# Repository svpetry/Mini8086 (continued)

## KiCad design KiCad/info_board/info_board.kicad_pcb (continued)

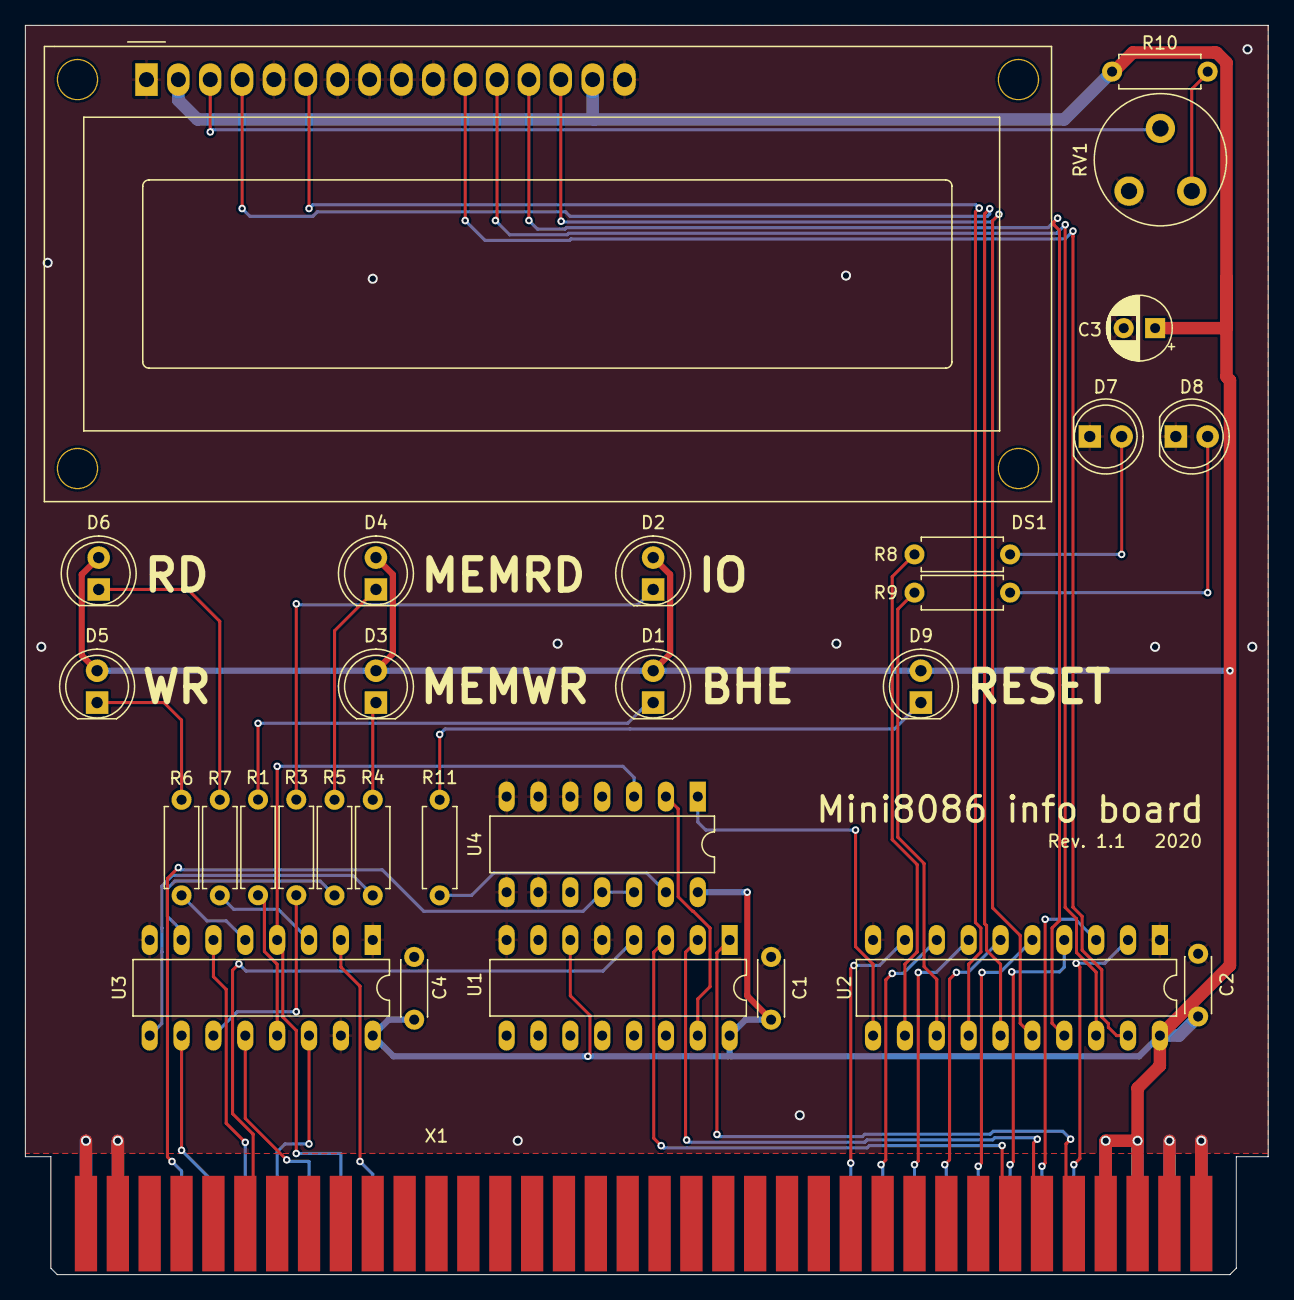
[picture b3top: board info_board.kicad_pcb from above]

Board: 2 copper layers, 99.1 x 99.6 mm, 30 parts (0 on the bottom side), 49 nets.

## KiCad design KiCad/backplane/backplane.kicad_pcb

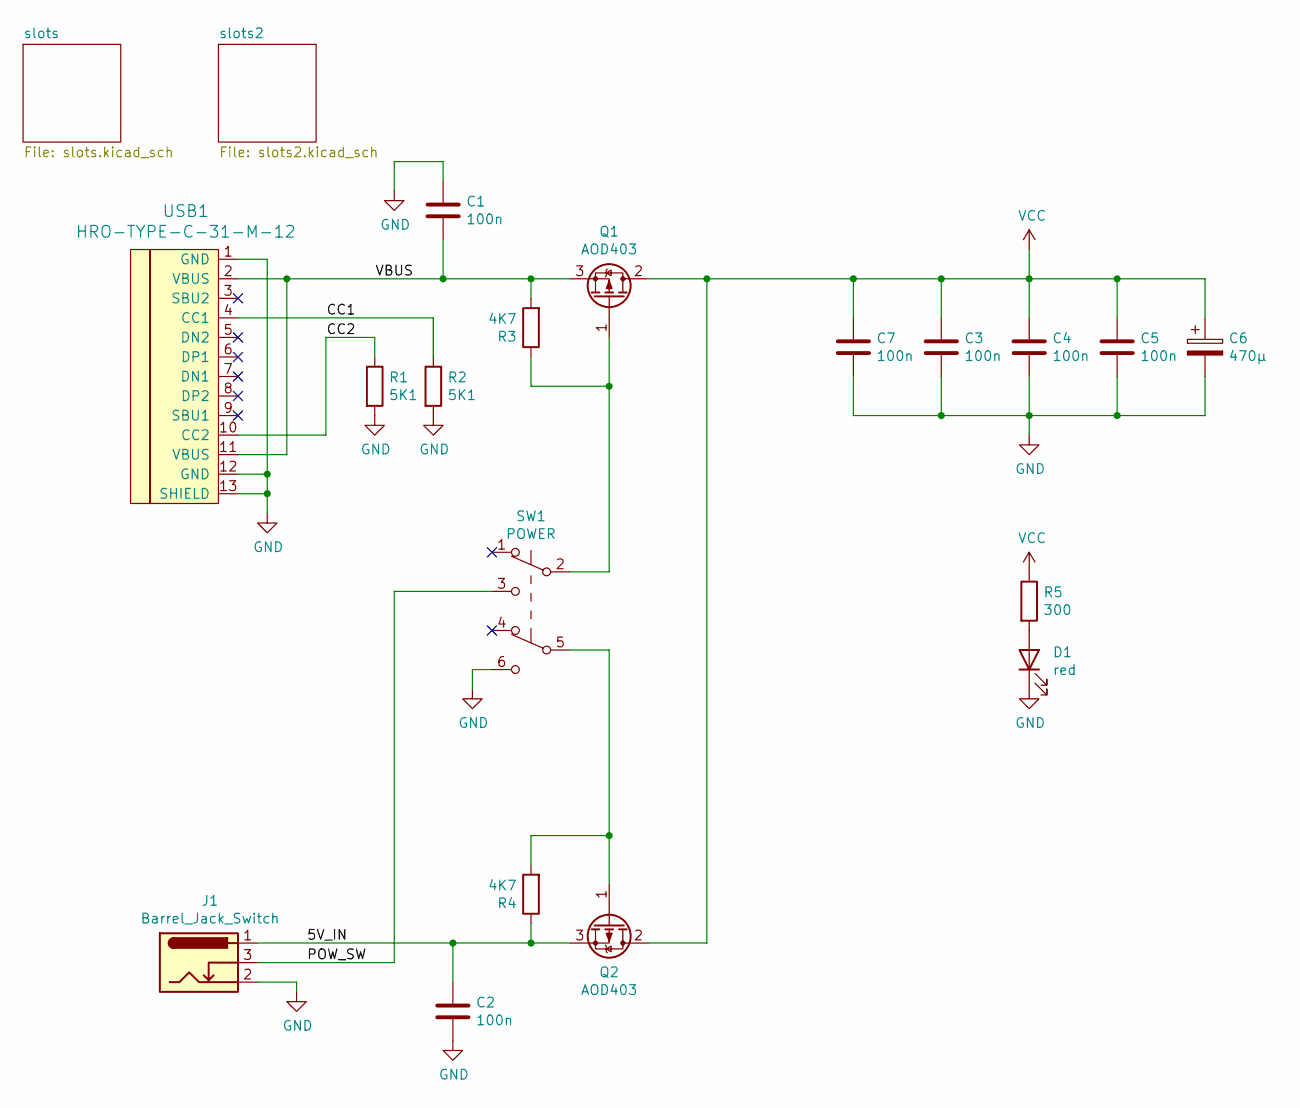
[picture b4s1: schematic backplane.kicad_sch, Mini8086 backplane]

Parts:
C1, C2: 100n; C_1206_3216Metric
C3, C4, C5, C7: 100n; C_Disc_D5.0mm_W2.5mm_P5.00mm
C6: 470µ; CP_Radial_D8.0mm_P3.80mm
D1: red; LED_1206_3216Metric_Castellated
J1: Barrel_Jack_Switch; BarrelJack_Horizontal
Q1, Q2: AOD403; TO-252-2
R1, R2: 5K1; R_1206_3216Metric
R3, R4: 4K7; R_1206_3216Metric
R5: 300; R_1206_3216Metric
SW1: POWER; Button
USB1: HRO-TYPE-C-31-M-12

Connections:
/5V_IN: C2.1, J1.1, Q2.3 (S), R4.1
/CC1: R2.1, USB1.4 (CC1)
/CC2: R1.1, USB1.10 (CC2)
/POW_SW: J1.3, SW1.3 (C)
/VBUS: C1.2, Q1.3 (S), R3.2, USB1.2 (VBUS), USB1.11 (VBUS)
GND: C1.1, C2.2, C3.2, C4.2, C5.2, C6.2, C7.2, D1.1 (K), J1.2, R1.2, R2.2, SW1.6 (C), USB1.1 (GND), USB1.12 (GND), USB1.13 (SHIELD); also elsewhere on the board
unnamed: D1.2 (A), R5.2
unnamed: Q1.1 (G), R3.1, SW1.2 (B)
unnamed: Q2.1 (G), R4.2, SW1.5 (B)
VCC: C3.1, C4.1, C5.1, C6.1, C7.1, Q1.2 (D), Q2.2 (D), R5.1; also elsewhere on the board

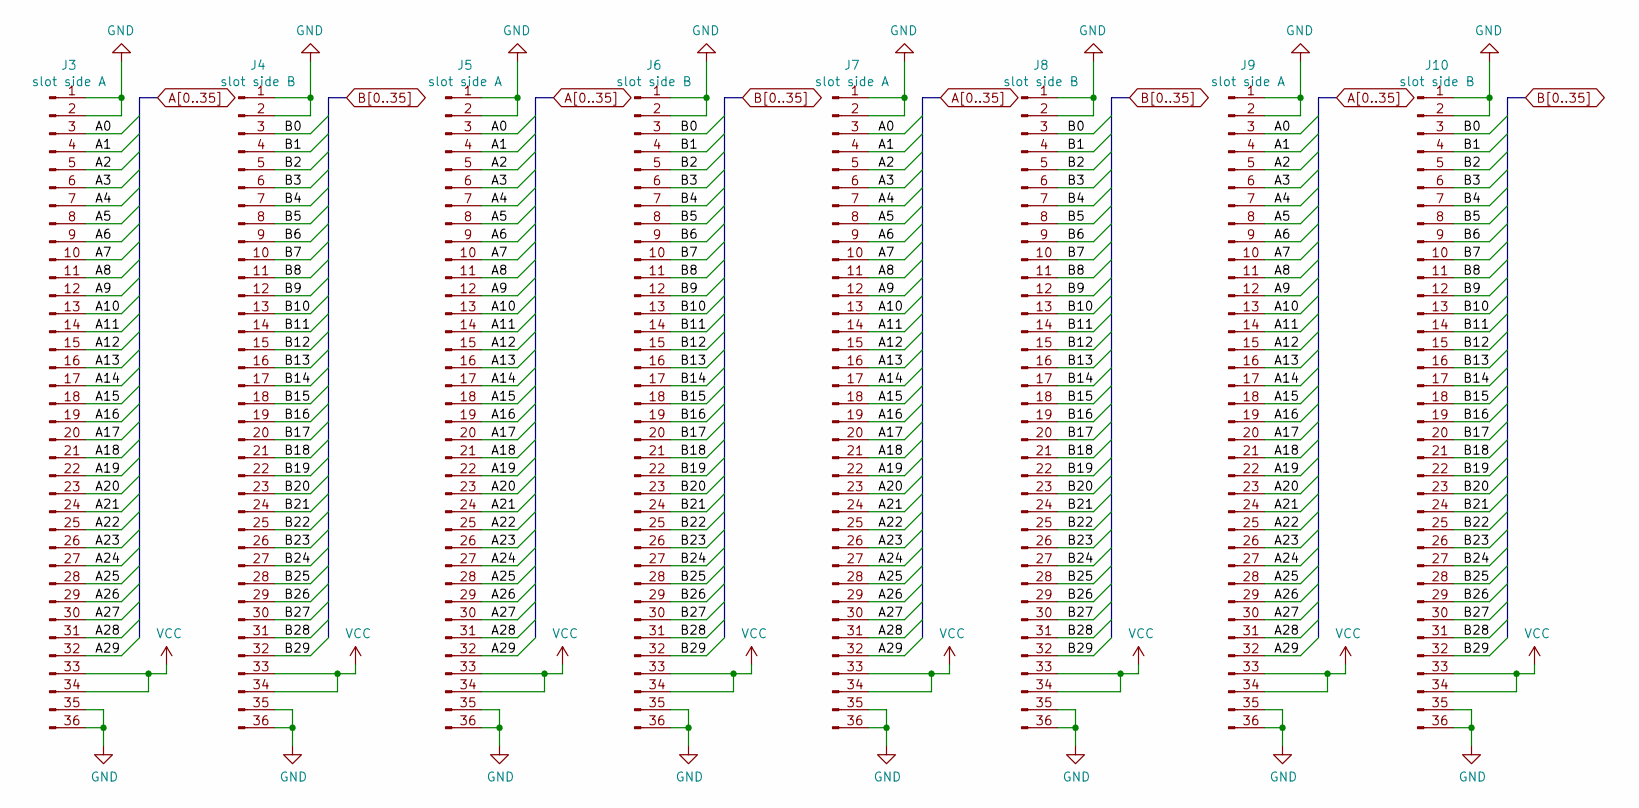
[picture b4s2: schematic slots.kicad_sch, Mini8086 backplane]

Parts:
J3, J5, J7, J9: slot side A; PinHeader_1x36_P2.54mm_Vertical
J4, J6, J8, J10: slot side B; PinHeader_1x36_P2.54mm_Vertical

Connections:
A0: J3.3, J5.3, J7.3, J9.3; also elsewhere on the board
A1: J3.4, J5.4, J7.4, J9.4; also elsewhere on the board
A2: J3.5, J5.5, J7.5, J9.5; also elsewhere on the board
A3: J3.6, J5.6, J7.6, J9.6; also elsewhere on the board
A4: J3.7, J5.7, J7.7, J9.7; also elsewhere on the board
A5: J3.8, J5.8, J7.8, J9.8; also elsewhere on the board
A6: J3.9, J5.9, J7.9, J9.9; also elsewhere on the board
A7: J3.10, J5.10, J7.10, J9.10; also elsewhere on the board
A8: J3.11, J5.11, J7.11, J9.11; also elsewhere on the board
A9: J3.12, J5.12, J7.12, J9.12; also elsewhere on the board
A10: J3.13, J5.13, J7.13, J9.13; also elsewhere on the board
A11: J3.14, J5.14, J7.14, J9.14; also elsewhere on the board
A12: J3.15, J5.15, J7.15, J9.15; also elsewhere on the board
A13: J3.16, J5.16, J7.16, J9.16; also elsewhere on the board
A14: J3.17, J5.17, J7.17, J9.17; also elsewhere on the board
A15: J3.18, J5.18, J7.18, J9.18; also elsewhere on the board
A16: J3.19, J5.19, J7.19, J9.19; also elsewhere on the board
A17: J3.20, J5.20, J7.20, J9.20; also elsewhere on the board
A18: J3.21, J5.21, J7.21, J9.21; also elsewhere on the board
A19: J3.22, J5.22, J7.22, J9.22; also elsewhere on the board
A20: J3.23, J5.23, J7.23, J9.23; also elsewhere on the board
A21: J3.24, J5.24, J7.24, J9.24; also elsewhere on the board
A22: J3.25, J5.25, J7.25, J9.25; also elsewhere on the board
A23: J3.26, J5.26, J7.26, J9.26; also elsewhere on the board
A24: J3.27, J5.27, J7.27, J9.27; also elsewhere on the board
A25: J3.28, J5.28, J7.28, J9.28; also elsewhere on the board
A26: J3.29, J5.29, J7.29, J9.29; also elsewhere on the board
A27: J3.30, J5.30, J7.30, J9.30; also elsewhere on the board
A28: J3.31, J5.31, J7.31, J9.31; also elsewhere on the board
A29: J3.32, J5.32, J7.32, J9.32; also elsewhere on the board
B0: J4.3, J6.3, J8.3, J10.3; also elsewhere on the board
B1: J4.4, J6.4, J8.4, J10.4; also elsewhere on the board
B2: J4.5, J6.5, J8.5, J10.5; also elsewhere on the board
B3: J4.6, J6.6, J8.6, J10.6; also elsewhere on the board
B4: J4.7, J6.7, J8.7, J10.7; also elsewhere on the board
B5: J4.8, J6.8, J8.8, J10.8; also elsewhere on the board
B6: J4.9, J6.9, J8.9, J10.9; also elsewhere on the board
B7: J4.10, J6.10, J8.10, J10.10; also elsewhere on the board
B8: J4.11, J6.11, J8.11, J10.11; also elsewhere on the board
B9: J4.12, J6.12, J8.12, J10.12; also elsewhere on the board
B10: J4.13, J6.13, J8.13, J10.13; also elsewhere on the board
B11: J4.14, J6.14, J8.14, J10.14; also elsewhere on the board
B12: J4.15, J6.15, J8.15, J10.15; also elsewhere on the board
B13: J4.16, J6.16, J8.16, J10.16; also elsewhere on the board
B14: J4.17, J6.17, J8.17, J10.17; also elsewhere on the board
B15: J4.18, J6.18, J8.18, J10.18; also elsewhere on the board
B16: J4.19, J6.19, J8.19, J10.19; also elsewhere on the board
B17: J4.20, J6.20, J8.20, J10.20; also elsewhere on the board
B18: J4.21, J6.21, J8.21, J10.21; also elsewhere on the board
B19: J4.22, J6.22, J8.22, J10.22; also elsewhere on the board
B20: J4.23, J6.23, J8.23, J10.23; also elsewhere on the board
B21: J4.24, J6.24, J8.24, J10.24; also elsewhere on the board
B22: J4.25, J6.25, J8.25, J10.25; also elsewhere on the board
B23: J4.26, J6.26, J8.26, J10.26; also elsewhere on the board
B24: J4.27, J6.27, J8.27, J10.27; also elsewhere on the board
B25: J4.28, J6.28, J8.28, J10.28; also elsewhere on the board
B26: J4.29, J6.29, J8.29, J10.29; also elsewhere on the board
B27: J4.30, J6.30, J8.30, J10.30; also elsewhere on the board
B28: J4.31, J6.31, J8.31, J10.31; also elsewhere on the board
B29: J4.32, J6.32, J8.32, J10.32; also elsewhere on the board
GND: J3.1, J3.2, J3.35, J3.36, J4.1, J4.2, J4.35, J4.36, J5.1, J5.2, J5.35, J5.36, J6.1, J6.2, J6.35, J6.36, J7.1, J7.2, J7.35, J7.36, J8.1, J8.2, J8.35, J8.36, J9.1, J9.2, J9.35, J9.36, J10.1, J10.2, J10.35, J10.36; also elsewhere on the board
VCC: J3.33, J3.34, J4.33, J4.34, J5.33, J5.34, J6.33, J6.34, J7.33, J7.34, J8.33, J8.34, J9.33, J9.34, J10.33, J10.34; also elsewhere on the board

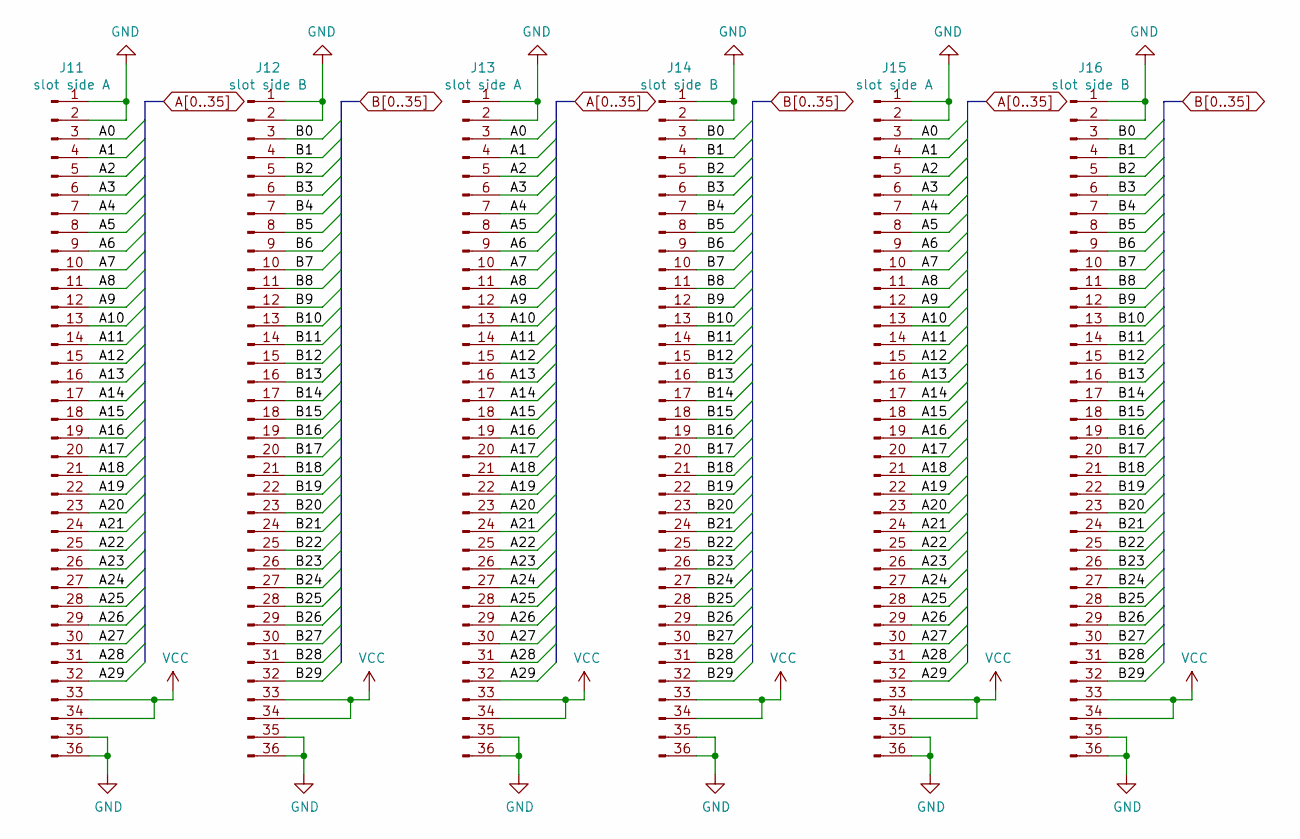
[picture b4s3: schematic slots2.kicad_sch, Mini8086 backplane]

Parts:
J11, J13, J15: slot side A; PinHeader_1x36_P2.54mm_Vertical
J12, J14, J16: slot side B; PinHeader_1x36_P2.54mm_Vertical

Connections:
A0: J11.3, J13.3, J15.3; also elsewhere on the board
A1: J11.4, J13.4, J15.4; also elsewhere on the board
A2: J11.5, J13.5, J15.5; also elsewhere on the board
A3: J11.6, J13.6, J15.6; also elsewhere on the board
A4: J11.7, J13.7, J15.7; also elsewhere on the board
A5: J11.8, J13.8, J15.8; also elsewhere on the board
A6: J11.9, J13.9, J15.9; also elsewhere on the board
A7: J11.10, J13.10, J15.10; also elsewhere on the board
A8: J11.11, J13.11, J15.11; also elsewhere on the board
A9: J11.12, J13.12, J15.12; also elsewhere on the board
A10: J11.13, J13.13, J15.13; also elsewhere on the board
A11: J11.14, J13.14, J15.14; also elsewhere on the board
A12: J11.15, J13.15, J15.15; also elsewhere on the board
A13: J11.16, J13.16, J15.16; also elsewhere on the board
A14: J11.17, J13.17, J15.17; also elsewhere on the board
A15: J11.18, J13.18, J15.18; also elsewhere on the board
A16: J11.19, J13.19, J15.19; also elsewhere on the board
A17: J11.20, J13.20, J15.20; also elsewhere on the board
A18: J11.21, J13.21, J15.21; also elsewhere on the board
A19: J11.22, J13.22, J15.22; also elsewhere on the board
A20: J11.23, J13.23, J15.23; also elsewhere on the board
A21: J11.24, J13.24, J15.24; also elsewhere on the board
A22: J11.25, J13.25, J15.25; also elsewhere on the board
A23: J11.26, J13.26, J15.26; also elsewhere on the board
A24: J11.27, J13.27, J15.27; also elsewhere on the board
A25: J11.28, J13.28, J15.28; also elsewhere on the board
A26: J11.29, J13.29, J15.29; also elsewhere on the board
A27: J11.30, J13.30, J15.30; also elsewhere on the board
A28: J11.31, J13.31, J15.31; also elsewhere on the board
A29: J11.32, J13.32, J15.32; also elsewhere on the board
B0: J12.3, J14.3, J16.3; also elsewhere on the board
B1: J12.4, J14.4, J16.4; also elsewhere on the board
B2: J12.5, J14.5, J16.5; also elsewhere on the board
B3: J12.6, J14.6, J16.6; also elsewhere on the board
B4: J12.7, J14.7, J16.7; also elsewhere on the board
B5: J12.8, J14.8, J16.8; also elsewhere on the board
B6: J12.9, J14.9, J16.9; also elsewhere on the board
B7: J12.10, J14.10, J16.10; also elsewhere on the board
B8: J12.11, J14.11, J16.11; also elsewhere on the board
B9: J12.12, J14.12, J16.12; also elsewhere on the board
B10: J12.13, J14.13, J16.13; also elsewhere on the board
B11: J12.14, J14.14, J16.14; also elsewhere on the board
B12: J12.15, J14.15, J16.15; also elsewhere on the board
B13: J12.16, J14.16, J16.16; also elsewhere on the board
B14: J12.17, J14.17, J16.17; also elsewhere on the board
B15: J12.18, J14.18, J16.18; also elsewhere on the board
B16: J12.19, J14.19, J16.19; also elsewhere on the board
B17: J12.20, J14.20, J16.20; also elsewhere on the board
B18: J12.21, J14.21, J16.21; also elsewhere on the board
B19: J12.22, J14.22, J16.22; also elsewhere on the board
B20: J12.23, J14.23, J16.23; also elsewhere on the board
B21: J12.24, J14.24, J16.24; also elsewhere on the board
B22: J12.25, J14.25, J16.25; also elsewhere on the board
B23: J12.26, J14.26, J16.26; also elsewhere on the board
B24: J12.27, J14.27, J16.27; also elsewhere on the board
B25: J12.28, J14.28, J16.28; also elsewhere on the board
B26: J12.29, J14.29, J16.29; also elsewhere on the board
B27: J12.30, J14.30, J16.30; also elsewhere on the board
B28: J12.31, J14.31, J16.31; also elsewhere on the board
B29: J12.32, J14.32, J16.32; also elsewhere on the board
GND: J11.1, J11.2, J11.35, J11.36, J12.1, J12.2, J12.35, J12.36, J13.1, J13.2, J13.35, J13.36, J14.1, J14.2, J14.35, J14.36, J15.1, J15.2, J15.35, J15.36, J16.1, J16.2, J16.35, J16.36; also elsewhere on the board
VCC: J11.33, J11.34, J12.33, J12.34, J13.33, J13.34, J14.33, J14.34, J15.33, J15.34, J16.33, J16.34; also elsewhere on the board

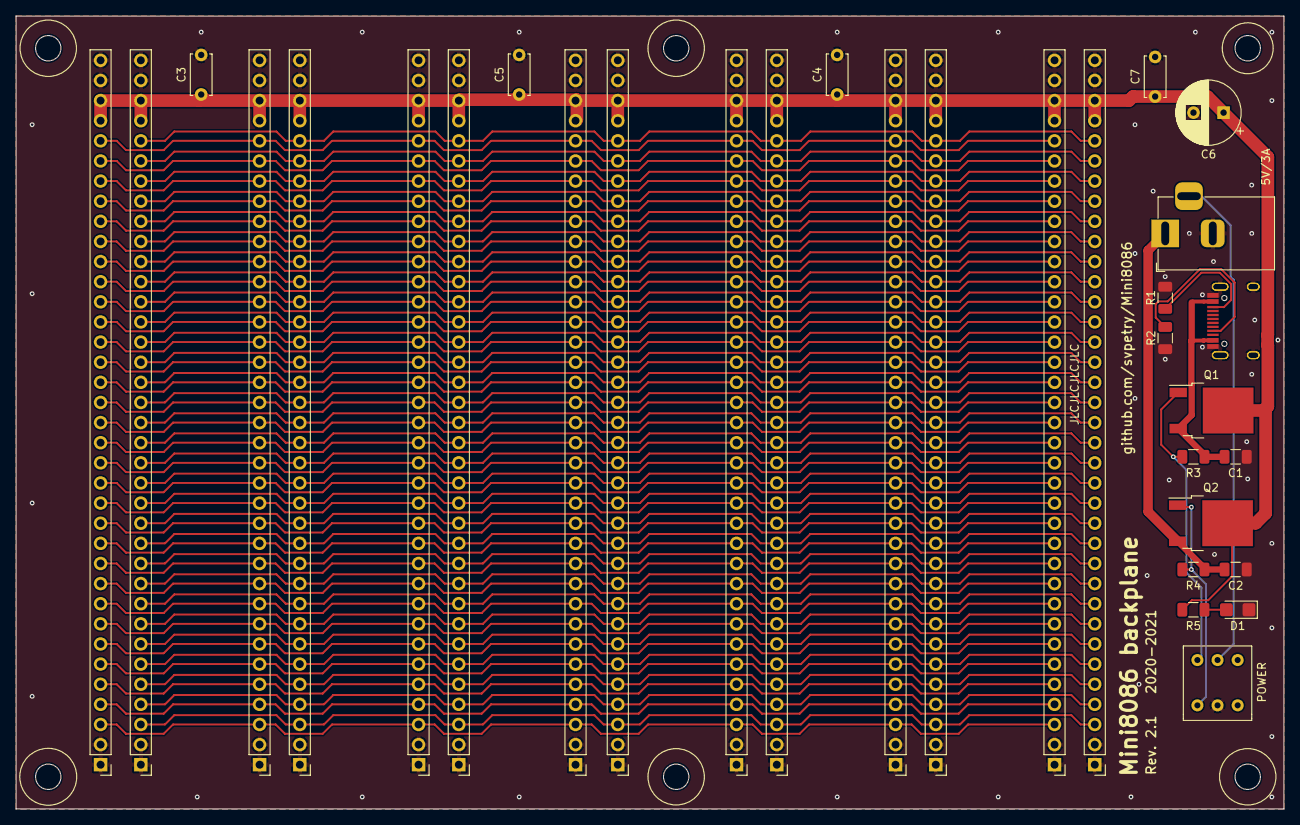
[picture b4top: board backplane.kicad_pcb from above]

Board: 2 copper layers, 160.0 x 100.1 mm, 32 parts (0 on the bottom side), 70 nets.

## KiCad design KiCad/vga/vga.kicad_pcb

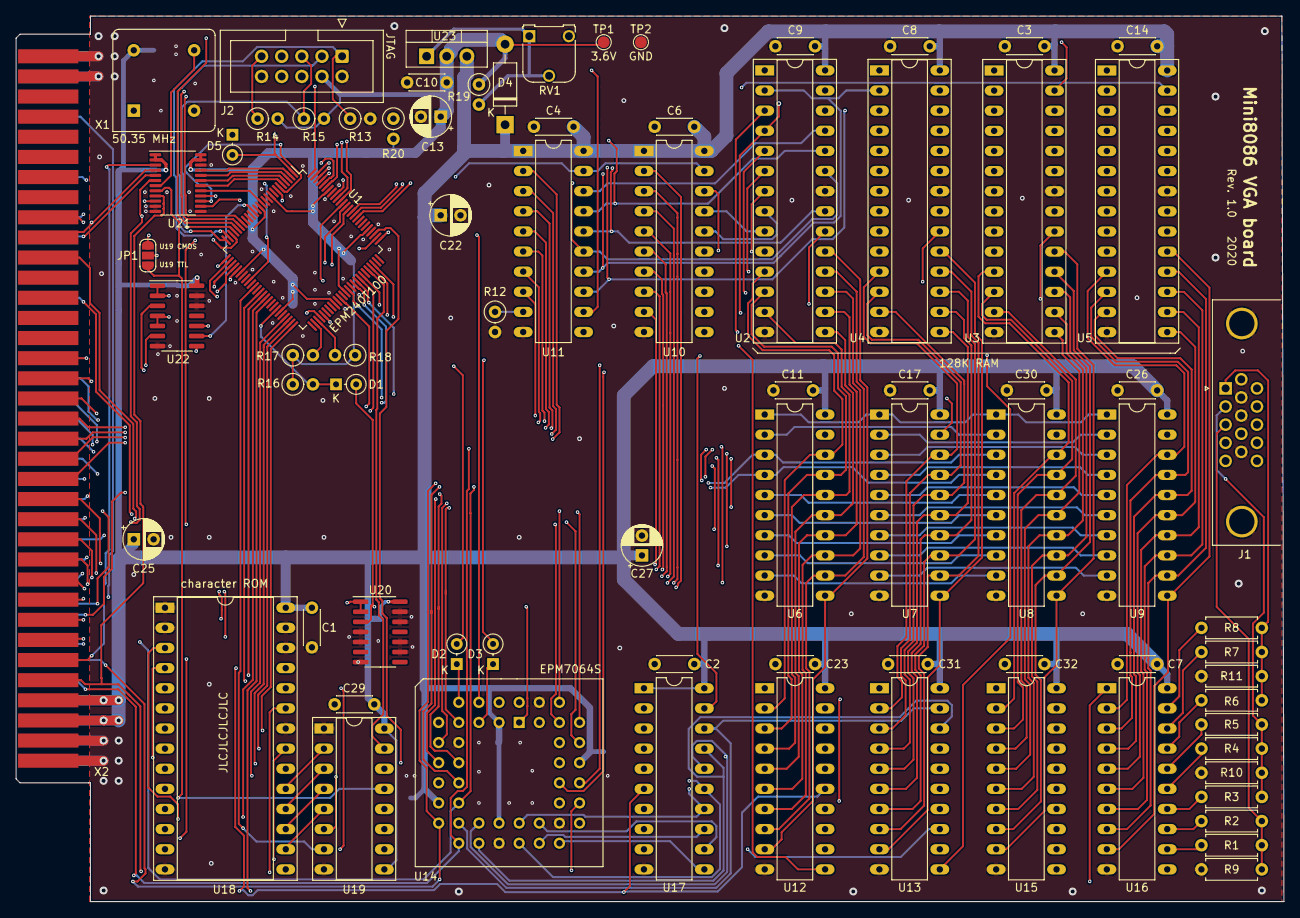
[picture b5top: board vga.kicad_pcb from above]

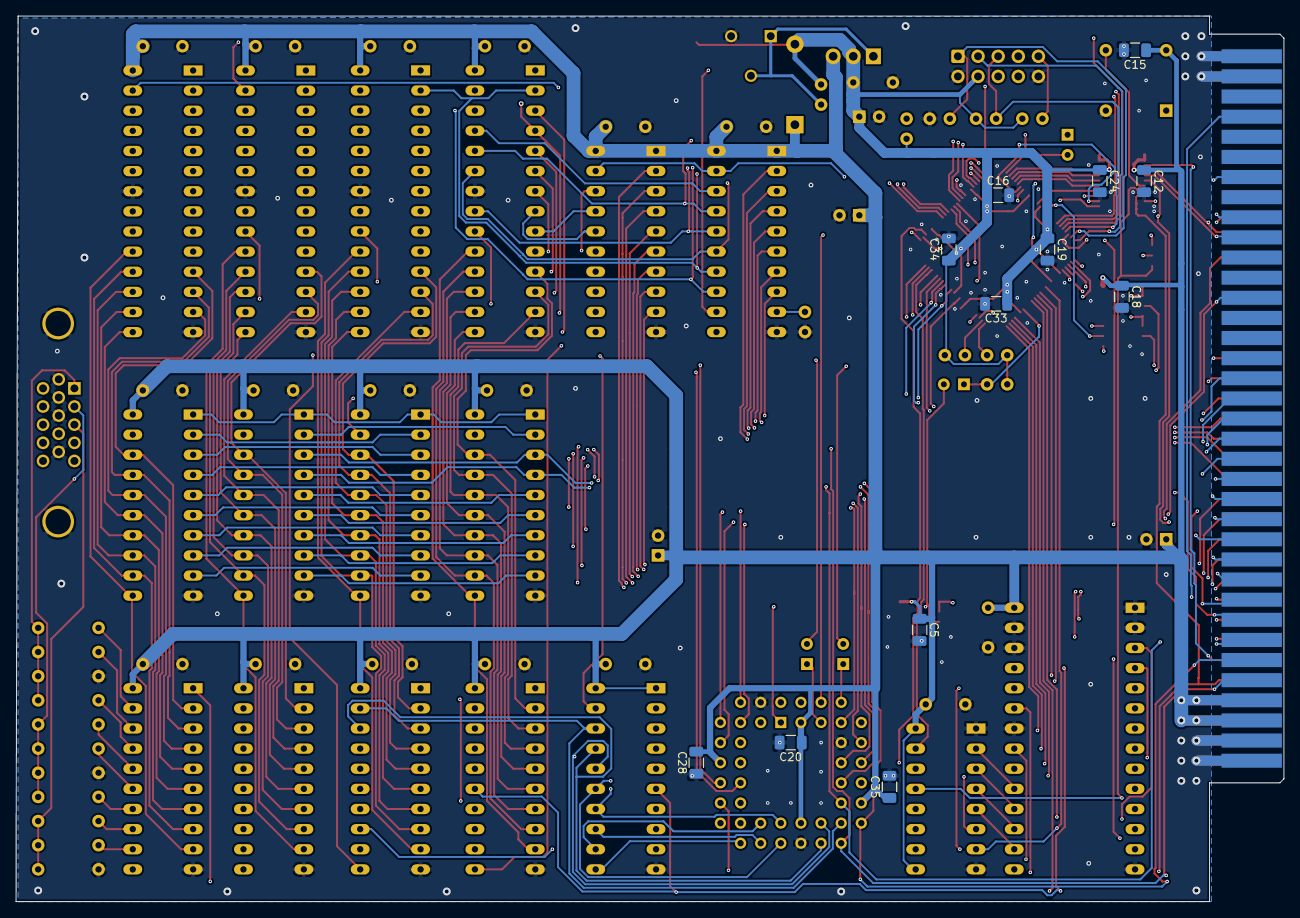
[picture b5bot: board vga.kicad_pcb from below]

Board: 4 copper layers, 160.0 x 111.8 mm, 90 parts (12 on the bottom side), 177 nets.

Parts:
C1, C2, C3, C4, C6, C7, C8, C9, C10, C11, C14, C17, C23, C26, C29, C30, C31, C32: 100n; C_Disc_D4.3mm_W1.9mm_P5.00mm
C5, C12, C15, C16, C18, C19, C20, C24, C28, C33, C34, C35: 100n; C_1206_3216Metric
C13, C25, C27: 10µ; CP_Radial_D5.0mm_P2.50mm
C22: 47µ; CP_Radial_D5.0mm_P2.50mm
D1, D2, D3, D5: BAT43; D_DO-34_SOD68_P2.54mm_Vertical_KathodeUp
D4: 1N4001; D_DO-41_SOD81_P10.16mm_Horizontal
J1: VGA connector; DSUB-15-HD_Female_Horizontal_P2.29x1.98mm_EdgePinOffset3.03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
J2: JTAG; IDC-Header_2x05_P2.54mm_Vertical
JP1: CHARPIXEL; SolderJumper-3_P1.3mm_Open_RoundedPad1.0x1.5mm_NumberLabels
R1, R3, R6: 500; R_Axial_DIN0207_L6.3mm_D2.5mm_P7.62mm_Horizontal
R2, R4, R7: 1K; R_Axial_DIN0207_L6.3mm_D2.5mm_P7.62mm_Horizontal
R5, R8: 2K; R_Axial_DIN0207_L6.3mm_D2.5mm_P7.62mm_Horizontal
R9: 56; R_Axial_DIN0207_L6.3mm_D2.5mm_P7.62mm_Horizontal
R10, R11: 47; R_Axial_DIN0207_L6.3mm_D2.5mm_P7.62mm_Horizontal
R12: 4K7; R_Axial_DIN0207_L6.3mm_D2.5mm_P2.54mm_Vertical
R13: 2K2; R_Axial_DIN0207_L6.3mm_D2.5mm_P2.54mm_Vertical
R14, R15: 10K; R_Axial_DIN0207_L6.3mm_D2.5mm_P2.54mm_Vertical
R16, R17, R18, R20: 1K; R_Axial_DIN0207_L6.3mm_D2.5mm_P2.54mm_Vertical
R19: 220; R_Axial_DIN0207_L6.3mm_D2.5mm_P2.54mm_Vertical
RV1: 500; Potentiometer_Runtron_RM-065_Vertical
TP1: 3.6V; TestPoint_Pad_D1.5mm
TP2: GND; TestPoint_Pad_D1.5mm
U1: EPM240T100; LQFP-100_14x14mm_P0.5mm
U2, U3, U4, U5: 61256-15; DIP-28_W7.62mm_Socket_LongPads
U6, U7, U8, U9, U10, U11: 74HC245; DIP-20_W7.62mm_LongPads
U12, U13, U15, U16: 74AC573; DIP-20_W7.62mm_LongPads
U14: EPM7064S; PLCC-44_THT-Socket
U17: 74AC245; DIP-20_W7.62mm_LongPads
U18: 27C512; DIP-28_W15.24mm_Socket_LongPads
U19: 74F166; DIP-16_W7.62mm_Socket_LongPads
U20: 74HC00; SOIC-14_3.9x8.7mm_P1.27mm
U21: 74LVC4245A; TSSOP-24_4.4x7.8mm_P0.65mm
U22: 74ACT32; SOIC-14_3.9x8.7mm_P1.27mm
U23: LM317_TO-220; TO-220-3_Vertical
X1: 50.35 MHz; Oscillator_DIP-8
X2: Edge72; BUS_72

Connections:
/CPLD/A0_3: U1.6, U21.15
/CPLD/A1_3: U1.2, U21.21
/CPLD/CHARPIXEL_CPLD: JP1.2, U1.77
/CPLD/CPLD_CLK: U21.7, X1.5
/CPLD/CPLD_CLK_3: U1.12, U21.17
/CPLD/HSYNC_3: U1.55, U22.4, U22.5
/CPLD/MODE0: D3.1, U14.5
/CPLD/MODE0_3: D3.2, R17.2, U1.52
/CPLD/MODE1: D2.1, U14.6
/CPLD/MODE1_3: D2.2, R18.2, U1.53
/CPLD/PLANE: D5.1, U14.41
/CPLD/PLANE_3: D5.2, R20.1, U1.1
/CPLD/TCK: J2.1, R13.1, U1.24
/CPLD/TDI: J2.9, R14.1, U1.23
/CPLD/TDO: J2.3, U1.25
/CPLD/TMS: J2.5, R15.1, U1.22
/CPLD/VSYNC_3: U1.54, U22.1, U22.2
/CPLD/~BHE_3: U1.7, U21.14
/CPLD/~RD_3: U1.4, U21.19
/CPLD/~RESET_3: D1.1, R16.2, U1.44
/CPLD/~VGA_MEM_3: U1.3, U21.20
/CPLD/~WR_3: U1.5, U21.18
/connector/B: J1.3, R1.2, R2.2, R9.1
/connector/G: J1.2, R3.2, R4.2, R5.2, R10.1
/connector/R: J1.1, R6.2, R7.2, R8.2, R11.1
/connector/RESET: U20.1, U20.2, X2.69
A0: U14.31, U21.9, X2.5
A1: U14.29, U21.3, X2.6
A2: U10.2, X2.7
A3: U10.3, X2.8
A4: U10.4, X2.9
A5: U10.5, X2.10
A6: U10.6, X2.11
A7: U10.7, X2.12
A8: U10.8, X2.13
A9: U10.9, X2.14
A10: U11.2, X2.15
A11: U11.3, X2.16
A12: U11.4, X2.17
A13: U11.5, X2.18
A14: U11.6, X2.19
A15: U11.7, X2.20
A16: U11.8, X2.21
CHARPIXEL: JP1.1, U19.13, U21.8
CHARPIXEL_3: JP1.3, U21.16
CHROW0: U1.47, U18.10
CHROW1: U1.48, U18.9
CHROW2: U1.49, U18.8
CHROW3: U1.50, U18.7
CPU_RAM_DIR: U1.61, U6.1, U7.1, U8.1, U9.1
D0: U6.2, U8.2, U14.18, X2.41
D1: U6.3, U8.3, U14.17, X2.42
D2: U6.4, U8.4, U14.16, X2.43
D3: U6.5, U8.5, U14.14, X2.44
D4: U6.6, U8.6, U14.12, X2.45
D5: U6.7, U8.7, U14.11, X2.46
D6: U6.8, U8.8, U14.9, X2.47
D7: U6.9, U8.9, U14.8, X2.48
D8: U7.2, U9.2, X2.49
D9: U7.3, U9.3, X2.50
D10: U7.4, U9.4, X2.51
D11: U7.5, U9.5, X2.52
D12: U7.6, U9.6, X2.53
D13: U7.7, U9.7, X2.54
D14: U7.8, U9.8, X2.55
D15: U7.9, U9.9, X2.56
DCHR0: U12.19, U15.19, U17.2, U18.6
DCHR1: U12.18, U15.18, U17.3, U18.5
DCHR2: U12.17, U15.17, U17.4, U18.4
DCHR3: U12.16, U15.16, U17.5, U18.3
DCHR4: U12.15, U15.15, U17.6, U18.25
DCHR5: U12.14, U15.14, U17.7, U18.24
DCHR6: U12.13, U15.13, U17.8, U18.21
DCHR7: U12.12, U15.12, U17.9, U18.23
DCOL0: R8.1, U13.19, U14.19, U16.19, U17.18
DCOL1: R7.1, U13.18, U14.20, U16.18, U17.17
DCOL2: R6.1, U13.17, U14.21, U16.17, U17.16
DCOL3: R5.1, U13.16, U14.24, U16.16, U17.15
DCOL4: R4.1, U13.15, U14.25, U16.15, U17.14
DCOL5: R3.1, U13.14, U14.26, U16.14, U17.13
DCOL6: R2.1, U13.13, U14.27, U16.13, U17.12
DCOL7: R1.1, U13.12, U14.28, U16.12, U17.11
GND: C1.2, C2.2, C3.2, C4.2, C5.2, C6.2, C7.2, C8.2, C9.2, C10.2, C11.2, C12.2, C13.2, C14.2, C15.2, C16.2, C17.2, C18.2, C19.2, C20.2, C22.2, C23.2, C24.2, C25.2, C26.2, C27.2, C28.2, C29.2, C30.2, C31.2, C32.2, C33.2, C34.2, C35.2, J1.0, J1.6, J1.7, J1.8, J1.10, J2.2, J2.10, R9.2, R10.2, R11.2, R12.2, R13.2, RV1.3, TP2.1, U1.10, U1.11, U1.32, U1.46, U1.60, U1.65, U1.79, U1.93, U2.14, U2.22, U3.14, U3.22, U4.14, U4.22, U5.14, U5.22, U6.10, U7.10, U8.10, U9.10, U10.10, U11.10, U12.10, U13.10, U14.10, U14.22, U14.30, U14.42, U15.10, U16.10, U17.10, U18.1, U18.2, U18.14, U18.22, U18.26, U18.27, U19.1, U19.8, U20.4, U20.5, U20.7, U20.9, U20.10, U20.12, U20.13, U21.11, U21.12, U21.13, U21.22, U22.7, U22.12, U22.13, X1.4, X2.1, X2.2, X2.35, X2.36, X2.37, X2.38, X2.71, X2.72
HSYNC: J1.13, U14.33, U22.6
IRQ5: U14.40, X2.60
LATCH_CHR: U1.73, U12.11, U15.11
LATCH_COL: U1.72, U13.11, U16.11
unnamed: R12.1, U11.9
unnamed: R19.2, RV1.1, RV1.2, U23.1
unnamed: U18.11, U19.14
unnamed: U18.12, U19.12
unnamed: U18.13, U19.11
unnamed: U18.15, U19.10
unnamed: U18.16, U19.5
unnamed: U18.17, U19.4
unnamed: U18.18, U19.3
unnamed: U18.19, U19.2
PX_CLK: U1.36, U19.7
R0D0: U2.11, U6.18, U12.2
R0D1: U2.12, U6.17, U12.3
R0D2: U2.13, U6.16, U12.4
R0D3: U2.15, U6.15, U12.5
R0D4: U2.16, U6.14, U12.6
R0D5: U2.17, U6.13, U12.7
R0D6: U2.18, U6.12, U12.8
R0D7: U2.19, U6.11, U12.9
R1D0: U4.11, U7.18, U13.2
R1D1: U4.12, U7.17, U13.3
R1D2: U4.13, U7.16, U13.4
R1D3: U4.15, U7.15, U13.5
R1D4: U4.16, U7.14, U13.6
R1D5: U4.17, U7.13, U13.7
R1D6: U4.18, U7.12, U13.8
R1D7: U4.19, U7.11, U13.9
R2D0: U3.11, U8.18, U15.2
R2D1: U3.12, U8.17, U15.3
R2D2: U3.13, U8.16, U15.4
R2D3: U3.15, U8.15, U15.5
R2D4: U3.16, U8.14, U15.6
R2D5: U3.17, U8.13, U15.7
R2D6: U3.18, U8.12, U15.8
R2D7: U3.19, U8.11, U15.9
R3D0: U5.11, U9.18, U16.2
R3D1: U5.12, U9.17, U16.3
R3D2: U5.13, U9.16, U16.4
R3D3: U5.15, U9.15, U16.5
R3D4: U5.16, U9.14, U16.6
R3D5: U5.17, U9.13, U16.7
R3D6: U5.18, U9.12, U16.8
R3D7: U5.19, U9.11, U16.9
RA0: U1.84, U2.10, U3.10, U4.10, U5.10, U10.18
RA1: U1.85, U2.9, U3.9, U4.9, U5.9, U10.17
RA2: U1.86, U2.8, U3.8, U4.8, U5.8, U10.16
RA3: U1.87, U2.7, U3.7, U4.7, U5.7, U10.15
RA4: U1.88, U2.6, U3.6, U4.6, U5.6, U10.14
RA5: U1.89, U2.5, U3.5, U4.5, U5.5, U10.13
RA6: U1.90, U2.4, U3.4, U4.4, U5.4, U10.12
RA7: U1.91, U2.3, U3.3, U4.3, U5.3, U10.11
RA8: U1.92, U2.25, U3.25, U4.25, U5.25, U11.18
RA9: U1.95, U2.24, U3.24, U4.24, U5.24, U11.17
RA10: U1.96, U2.21, U3.21, U4.21, U5.21, U11.16
RA11: U1.97, U2.23, U3.23, U4.23, U5.23, U11.15
RA12: U1.98, U2.2, U3.2, U4.2, U5.2, U11.14
RA13: U1.99, U2.26, U3.26, U4.26, U5.26, U11.13
RA14: U1.100, U2.1, U3.1, U4.1, U5.1, U11.12
RDY1: U22.8, X2.28
VCC: C1.1, C2.1, C3.1, C4.1, C5.1, C6.1, C7.1, C8.1, C9.1, C11.1, C12.1, C14.1, C15.1, C17.1, C18.1, C20.1, C22.1, C23.1, C25.1, C26.1, C27.1, C28.1, C29.1, C30.1, C31.1, C32.1, C35.1, D4.1, U2.28, U3.28, U4.28, U5.28, U6.20, U7.20, U8.20, U9.20, U10.1, U10.20, U11.1, U11.20, U12.20, U13.20, U14.3, U14.15, U14.23, U14.35, U15.20, U16.20, U17.1, U17.20, U18.28, U19.9, U19.16, U20.14, U21.1, U21.2, U22.14, U23.3, X1.8, X2.3, X2.4, X2.39, X2.40
VCC36: C10.1, C13.1, C16.1, C19.1, C24.1, C33.1, C34.1, D4.2, J2.4, R14.2, R15.2, R16.1, R17.1, R18.1, R19.1, R20.2, TP1.1, U1.9, U1.13, U1.31, U1.45, U1.59, U1.63, U1.80, U1.94, U21.23, U21.24, U23.2
VSYNC: J1.14, U14.34, U22.3
~BHE: U21.10, X2.66
~BLOCK_CPU: U1.15, U22.9
~CHARMODE: U1.78, U18.20, U19.6
~CHAR_BG: U1.76, U14.4
~CHR_TO_COL: U1.69, U17.19
~CPU_RAM0: U1.68, U6.19
~CPU_RAM1: U1.67, U7.19
~CPU_RAM2: U1.66, U8.19
~CPU_RAM3: U1.64, U9.19
~CPU_RAM_ADDR: U1.34, U10.19, U11.19
~CS_R0: U1.27, U2.20
~CS_R1: U1.28, U4.20
~CS_R2: U1.29, U3.20
~CS_R3: U1.30, U5.20
~OE_L0: U1.38, U12.1
~OE_L1: U1.39, U13.1
~OE_L2: U1.40, U15.1
~OE_L3: U1.41, U16.1
~PE_CHPX: U1.71, U19.15
~RD: U21.5, X2.63
~RESET: D1.2, U14.1, U20.3
~VGA_IO: U14.39, X2.26
~VGA_MEM: U21.4, U22.10, X2.27
~WE_R0: U1.19, U2.27
~WE_R1: U1.20, U4.27
~WE_R2: U1.21, U3.27
~WE_R3: U1.26, U5.27
~WR: U14.37, U21.6, X2.64
